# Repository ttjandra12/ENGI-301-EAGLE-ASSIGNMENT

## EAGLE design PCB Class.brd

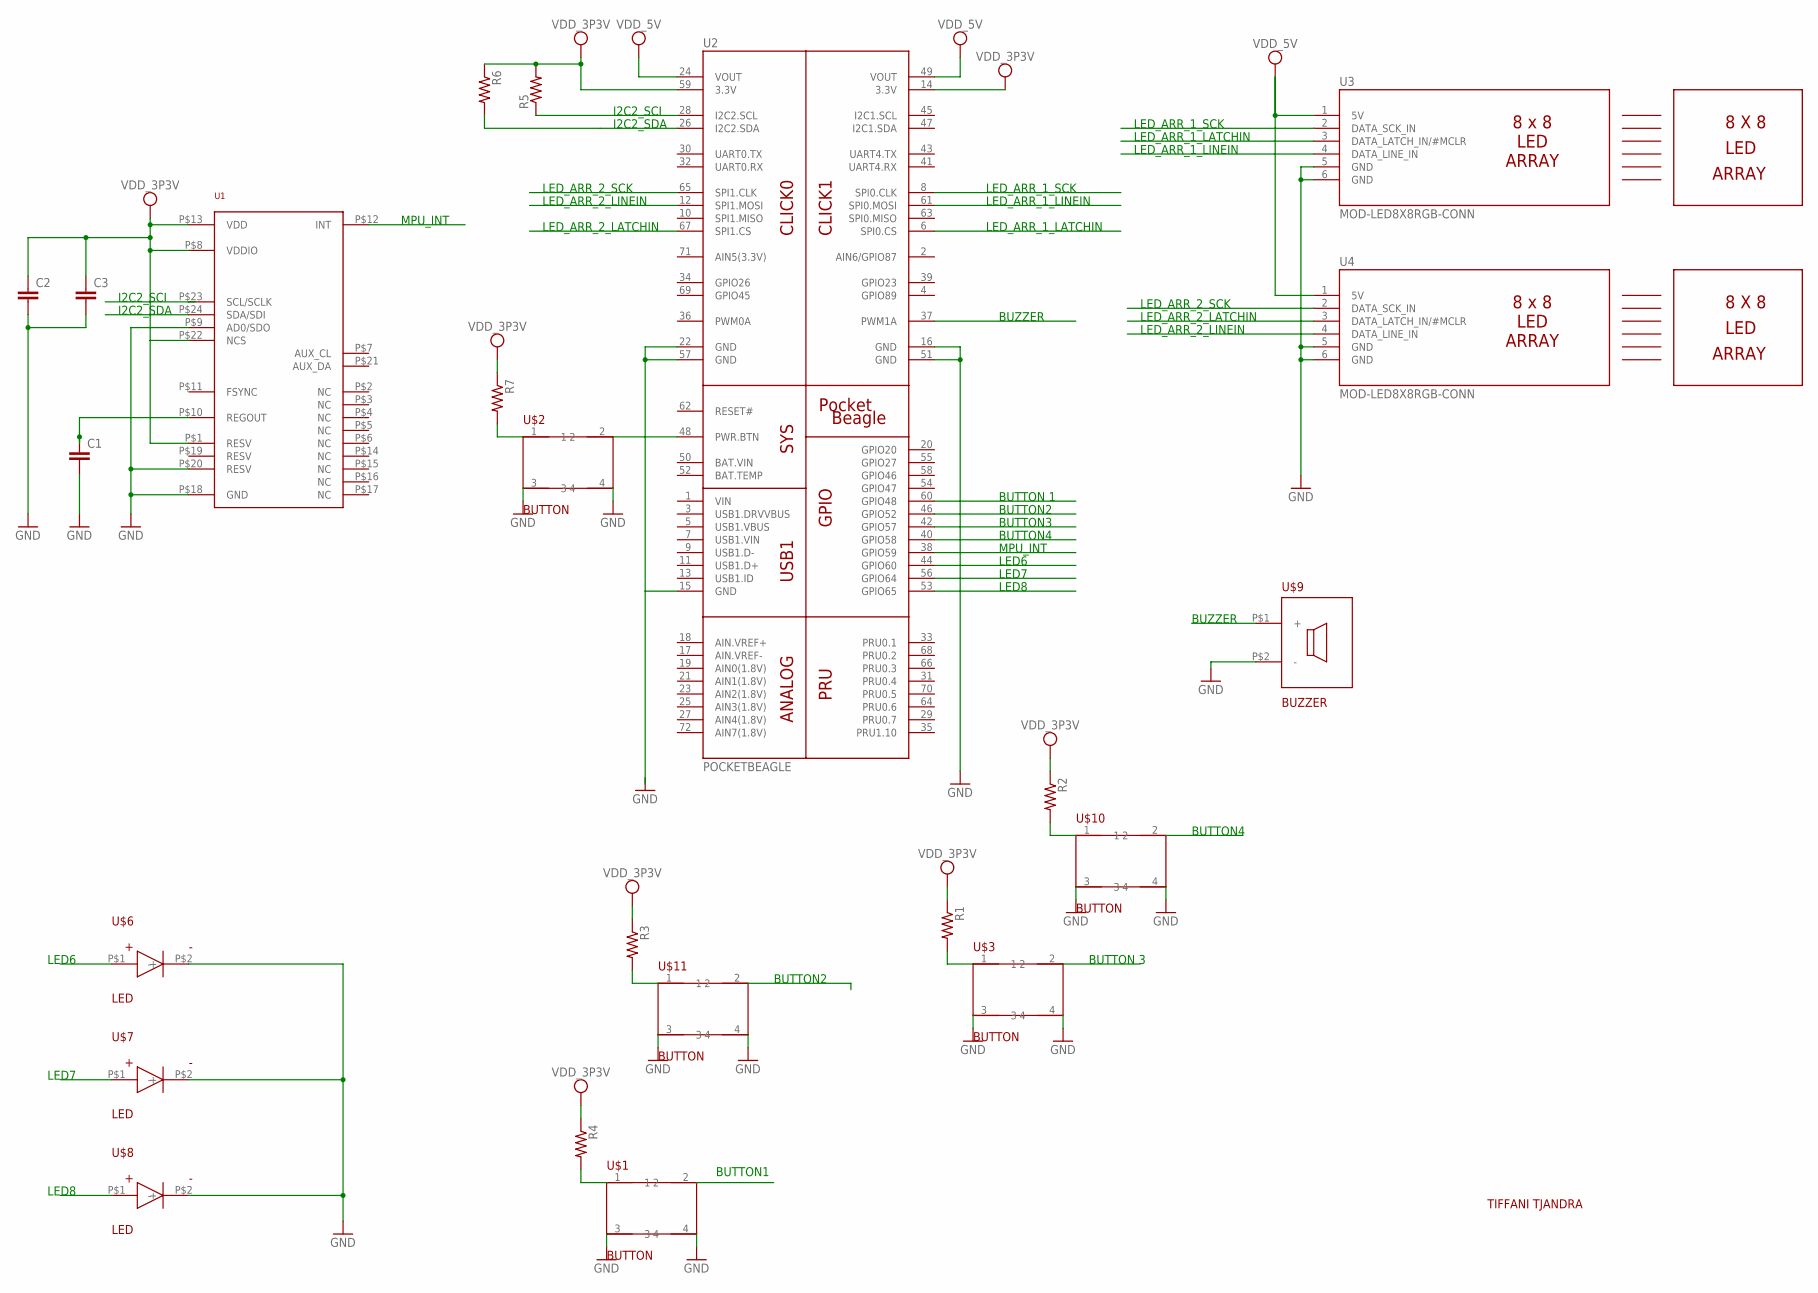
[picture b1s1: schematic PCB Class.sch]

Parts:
C1, C2, C3: C_C0402; C0402
R1, R2, R3, R4, R7: R_R6332W; R6332W
R5, R6: R_R0402; R0402
U1: MPU-9250; PROJECT01
U2: POCKETBEAGLE
U3, U4: MOD-LED8X8RGB-CONN; FE06W
U$1, U$2, U$3, U$10, U$11: BUTTON
U$6, U$7, U$8: LED
U$9: BUZZER

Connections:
GND: C1.2, C2.2, C3.2, U1.P$9 (AD0/SDO), U1.P$18 (GND), U1.P$20 (RESV), U2.16 (GND), U2.51 (GND), U3.5 (GND), U3.6 (GND), U4.5 (GND), U4.6 (GND), U$1.3, U$1.4, U$2.3, U$2.4, U$3.3, U$3.4, U$6.P$2 (-), U$7.P$2 (-), U$8.P$2 (-), U$9.P$2 (-), U$10.3, U$10.4, U$11.3, U$11.4
unnamed: R1.2, U$3.1
unnamed: R3.2, U$11.1
unnamed: R4.2, U$1.1
unnamed: R2.2, U$10.1
unnamed: U2.15 (GND), U2.22 (GND), U2.57 (GND)
unnamed: C1.1, U1.P$10 (REGOUT)
unnamed: R6.2, U2.26 (I2C2.SDA)
unnamed: R5.1, U2.28 (I2C2.SCL)
unnamed: R7.2, U$2.1
SYS_VDD1_3P3V: C2.1, C3.1, R1.1, R2.1, R3.1, R4.1, R5.2, R6.1, R7.1, U1.P$1 (RESV), U1.P$8 (VDDIO), U1.P$13 (VDD), U1.P$22 (NCS), U2.14 (3.3V), U2.24 (VOUT), U2.49 (VOUT), U2.59 (3.3V), U3.1 (5V), U4.1 (5V)

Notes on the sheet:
TIFFANI TJANDRA
8 X 8
LED
ARRAY
LED6
LED7
LED8
BUTTON4
BUTTON 3
BUTTON2
BUTTON1
BUTTON3
BUTTON 1
BUZZER
LED_ARR_1_LATCHIN
LED_ARR_1_LINEIN
LED_ARR_1_SCK
LED_ARR_2_SCK
LED_ARR_2_LATCHIN
LED_ARR_2_LINEIN
MPU_INT
I2C2_SCI
I2C2_SDA

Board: 4 copper layers, 23 parts (0 on the bottom side), 11 nets, no tracks yet.
